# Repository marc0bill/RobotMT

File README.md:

# Project Robot Polytech département MT

Le projet consiste à réaliser un robot automne de type "coupe de France de robotique (Eurobot)".
Le robot MT contient une batterie, des moteurs et des capteurs. Des UCEs (Unité de commande électronique) sont mis en place pour gérer les différents périphériques du robot. Ces UCEs ou ECU(acronyme Anglais) se communiquent par le bus CAN. Le choix du protocole CAN est expliqué dans les Wikis.  

## Getting Started
Vous trouvez dans le dossier de ce projet:
-le dossier "carte": les schémas des UCEs employées.
-le dossier "Firmware": les firmwares des UCEs codé en C. (le principe de la compilation conditionnelle est utilisé dans le code => Un seul projet.X peut servir pour implémenter deux firmware différents sur deux UCEs différentes. Il suffit de de changer le nom du node dans le fichier node.h du projet.X )
-Le dossier python: Les codes pythons utilisées.

### Prerequisites

Logiciel à télécharger:

On utilise des contrôleurs de type dsPIC33FJ128MC804(digital signal controler) (Microchip), il faudrait donc télécharger :
```
MPLAPX IDE
```

```
Compilateur XC16
```

Des schémas électriques des UCEs sont disponible en format .pdf, mais si vous souhaitez les modifier ou voir une vision plus profonde, il faudrait télécharger :
```
EAGLE
```

Pour visualiser les données reçus par l'UART sur votre PC, téléchargez une application terminale simple de porte série 
```
Termite
```
ou
```
CoolTerm
```

=======
# Projet Robot Polytech département MT

Le département Microélectronique et Télécommunications de Polytech Marseille développe son propre robot de A à Z. Chaque année le projet s'améliore grâce aux élèves de 4ème année. Ce robot, de type coupe de France de robotique, peut se déplacer de façon autonome dans son environnement, déplacer des objets, et ramasser des balles (tennis ou ping-pong).

## Getting Started

These instructions will get you a copy of the project up and running on your local machine for development and testing purposes. See deployment for notes on how to deploy the project on a live system.

### Prerequisites

What things you need to install the software and how to install them

```
Give examples
```

### Installing

A step by step series of examples that tell you have to get a development env running

Say what the step will be

```
Give the example
```

And repeat

```
until finished
```

End with an example of getting some data out of the system or using it for a little demo

## Running the tests

Explain how to run the automated tests for this system

### Break down into end to end tests

Explain what these tests test and why

```
Give an example
```

### And coding style tests

Explain what these tests test and why

```
Give an example
```

## Contributing

Please read [CONTRIBUTING.md](https://gist.github.com/PurpleBooth/b24679402957c63ec426) for details on our code of conduct, and the process for submitting pull requests to us.

## Versioning

We use [SemVer](http://semver.org/) for versioning. For the versions available, see the [tags on this repository](https://github.com/your/project/tags). 

## Authors

* **Marc Bocquet** - *Initial work* - [marc0bill](https://github.com/marc0bill)

See also the list of [contributors](https://github.com/your/project/contributors) who participated in this project.

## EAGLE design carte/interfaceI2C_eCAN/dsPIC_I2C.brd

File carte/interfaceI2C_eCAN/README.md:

# Carte interface eCAN/I2C/UART/entrée Analog

## Présentation

La carte proposé ici, permet l'interface entre le bus eCAN et d'autre périférique (comme par exemple les modules ultrason en I2C ou capteur de distance SHARP analogique)

## Détail

Deux versions de cartes sont proposées : 

### dsPIC_I2C

Il s'agit de celle actuellement utilisé et fonctionnelle

### dsPIC_I2CMini

Il s'agit d'une version plus compact à finaliser si nécessaire.
Un travail sur les connecteurs pourrait aussi être effectuer pour amélioré la robustesse d'assemblage et la taille de la carte.

### firmware

Le firmware associé a cette carte est :

```
firmware/dsPICeCAN.X
```

## Authors

* **Marc Bocquet** - *Initial work* - [marc0bill](https://github.com/marc0bill)

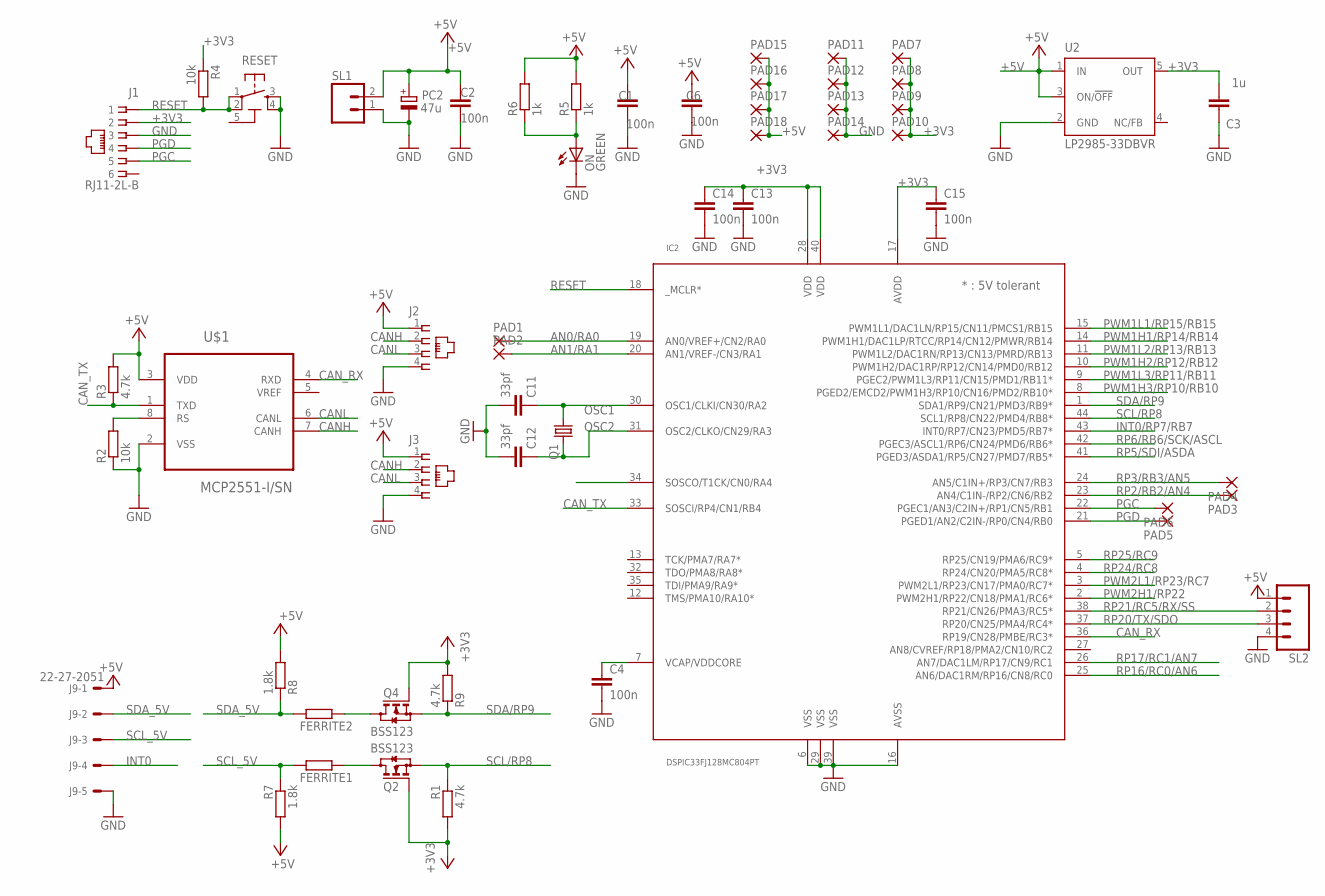
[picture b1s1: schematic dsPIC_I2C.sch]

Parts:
C1, C2: 100n; C0603-ROUND
C3: 1u; C0603-ROUND
C4, C6: 100n; C0603K
C11, C12: 33pf; C0603
C13, C14, C15: 100n; C0603
FERRITE1, FERRITE2: R-EU_M0805; M0805
IC2: DSPIC33FJ128MC804PT; TQFP44
J1: RJ11-2L-B; RJ11-NO_SHIELD
J2, J3: 520249-2
J9: 22-27-2051; 6410-05
ON: GREEN; CHIP-LED0805
PAD1, PAD2, PAD3, PAD4, PAD5, PAD6, PAD7, PAD8, PAD9, PAD10, PAD11, PAD12, PAD13, PAD14, PAD15, PAD16, PAD17, PAD18: 1,6/0,9
PC2: 47u; PANASONIC_D
Q1: CRYSTALSM49; SM49
Q2, Q4: BSS123; SOT23
R1, R3, R9: 4.7k; R0805
R2, R4: 10k; R0805
R5, R6: 1k; R0805
R7, R8: 1.8k; 0204/7
RESET: TS42031-160R-TR-7260; TS42
SL1: M02; 02P
SL2: M04; 04P
U2: LP2985-33DBVR; SOT23-DBV
U$1: MCP2551-I/SN; SOIC127P600X175-8N

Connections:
5-GND: RESET.5 (5-GND)
+3V3: C3.2, C13.1, C14.1, C15.1, IC2.17 (AVDD), IC2.28 (VDD), IC2.40 (VDD), J1.2, PAD7.1, PAD8.1, PAD9.1, PAD10.1, Q2.1 (G), Q4.1 (G), R1.2, R4.1, R9.2, U2.5 (OUT)
+5V: C1.2, C2.2, C6.2, J2.1, J3.1, J9.1, PAD15.1, PAD16.1, PAD17.1, PAD18.1, PC2.+, R3.2, R5.2, R6.2, R7.2, R8.2, SL1.2, SL2.1, U2.1 (IN), U2.3 (ON/!OFF), U$1.3 (VDD)
AN0/RA0: IC2.19 (AN0/VREF+/CN2/RA0), PAD1.1
AN1/RA1: IC2.20 (AN1/VREF-/CN3/RA1), PAD2.1
ASCL: FERRITE1.2, Q2.3 (D)
ASDA: FERRITE2.2, Q4.3 (D)
CANH: J2.2, J3.2, U$1.7 (CANH)
CANL: J2.3, J3.3, U$1.6 (CANL)
CAN_RX: IC2.36 (RP19/CN28/PMBE/RC3*), U$1.4 (RXD)
CAN_TX: IC2.33 (SOSCI/RP4/CN1/RB4), R3.1, U$1.1 (TXD)
GND: C1.1, C2.1, C3.1, C4.2, C6.1, C11.2, C12.2, C13.2, C14.2, C15.2, IC2.6 (VSS), IC2.16 (AVSS), IC2.29 (VSS), IC2.39 (VSS), J1.3, J2.4, J3.4, J9.5, ON.C, PAD11.1, PAD12.1, PAD13.1, PAD14.1, PC2.-, R2.1, RESET.3, RESET.4, SL1.1, SL2.4, U2.2 (GND), U$1.2 (VSS)
INT0: J9.4
INT0/RP7/RB7: IC2.43 (INT0/RP7/CN23/PMD5/RB7*)
unnamed: ON.A, R5.1, R6.1
unnamed: C4.1, IC2.7 (VCAP/VDDCORE)
unnamed: R2.2, U$1.8 (RS)
OSC1: C11.1, IC2.30 (OSC1/CLKI/CN30/RA2), Q1.1
OSC2: C12.1, IC2.31 (OSC2/CLKO/CN29/RA3), Q1.2
PGC: IC2.22 (PGEC1/AN3/C2IN+/RP1/CN5/RB1), J1.5, PAD6.1
PGD: IC2.21 (PGED1/AN2/C2IN-/RP0/CN4/RB0), J1.4, PAD5.1
PWM1H1/RP14/RB14: IC2.14 (PWM1H1/DAC1LP/RTCC/RP14/CN12/PMWR/RB14)
PWM1H2/RP12/RB12: IC2.10 (PWM1H2/DAC1RP/RP12/CN14/PMD0/RB12)
PWM1H3/RP10/RB10: IC2.8 (PGED2/EMCD2/PWM1H3/RP10/CN16/PMD2/RB10*)
PWM1L1/RP15/RB15: IC2.15 (PWM1L1/DAC1LN/RP15/CN11/PMCS1/RB15)
PWM1L2/RP13/RB13: IC2.11 (PWM1L2/DAC1RN/RP13/CN13/PMRD/RB13)
PWM1L3/RP11/RB11: IC2.9 (PGEC2/PWM1L3/RP11/CN15/PMD1/RB11*)
PWM2H1/RP22: IC2.2 (PWM2H1/RP22/CN18/PMA1/RC6*)
PWM2L1/RP23/RC7: IC2.3 (PWM2L1/RP23/CN17/PMA0/RC7*)
RESET: IC2.18 (_MCLR*), J1.1, R4.2, RESET.1, RESET.2
RP2/RB2/AN4: IC2.23 (AN4/C1IN-/RP2/CN6/RB2), PAD3.1
RP3/RB3/AN5: IC2.24 (AN5/C1IN+/RP3/CN7/RB3), PAD4.1
RP5/SDI/ASDA: IC2.41 (PGED3/ASDA1/RP5/CN27/PMD7/RB5*)
RP6/RB6/SCK/ASCL: IC2.42 (PGEC3/ASCL1/RP6/CN24/PMD6/RB6*)
RP16/RC0/AN6: IC2.25 (AN6/DAC1RM/RP16/CN8/RC0)
RP17/RC1/AN7: IC2.26 (AN7/DAC1LM/RP17/CN9/RC1)
RP20/TX/SDO: IC2.37 (RP20/CN25/PMA4/RC4*), SL2.3
RP21/RC5/RX/SS: IC2.38 (RP21/CN26/PMA3/RC5*), SL2.2
RP24/RC8: IC2.4 (RP24/CN20/PMA5/RC8*)
RP25/RC9: IC2.5 (RP25/CN19/PMA6/RC9*)
SCL/RP8: IC2.44 (SCL1/RP8/CN22/PMD4/RB8*), Q2.2 (S), R1.1
SCL_5V: FERRITE1.1, J9.3, R7.1
SDA/RP9: IC2.1 (SDA1/RP9/CN21/PMD3/RB9*), Q4.2 (S), R9.1
SDA_5V: FERRITE2.1, J9.2, R8.1

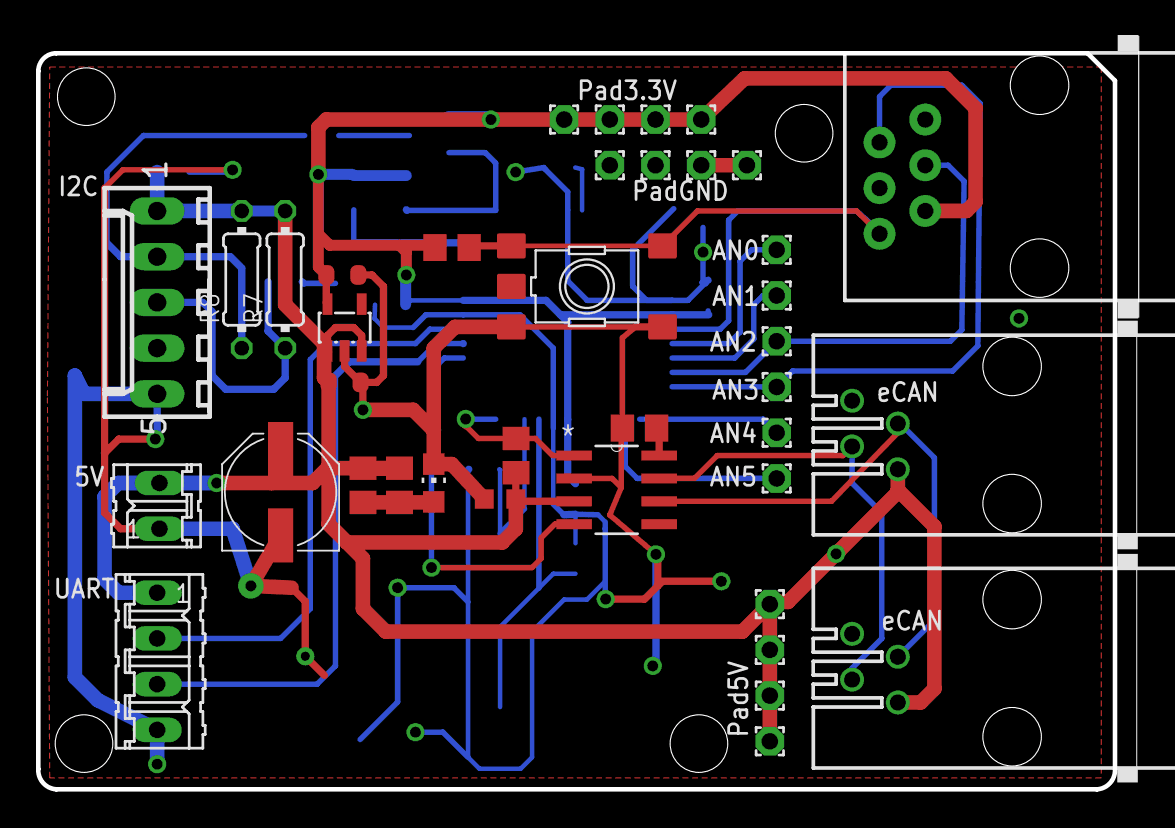
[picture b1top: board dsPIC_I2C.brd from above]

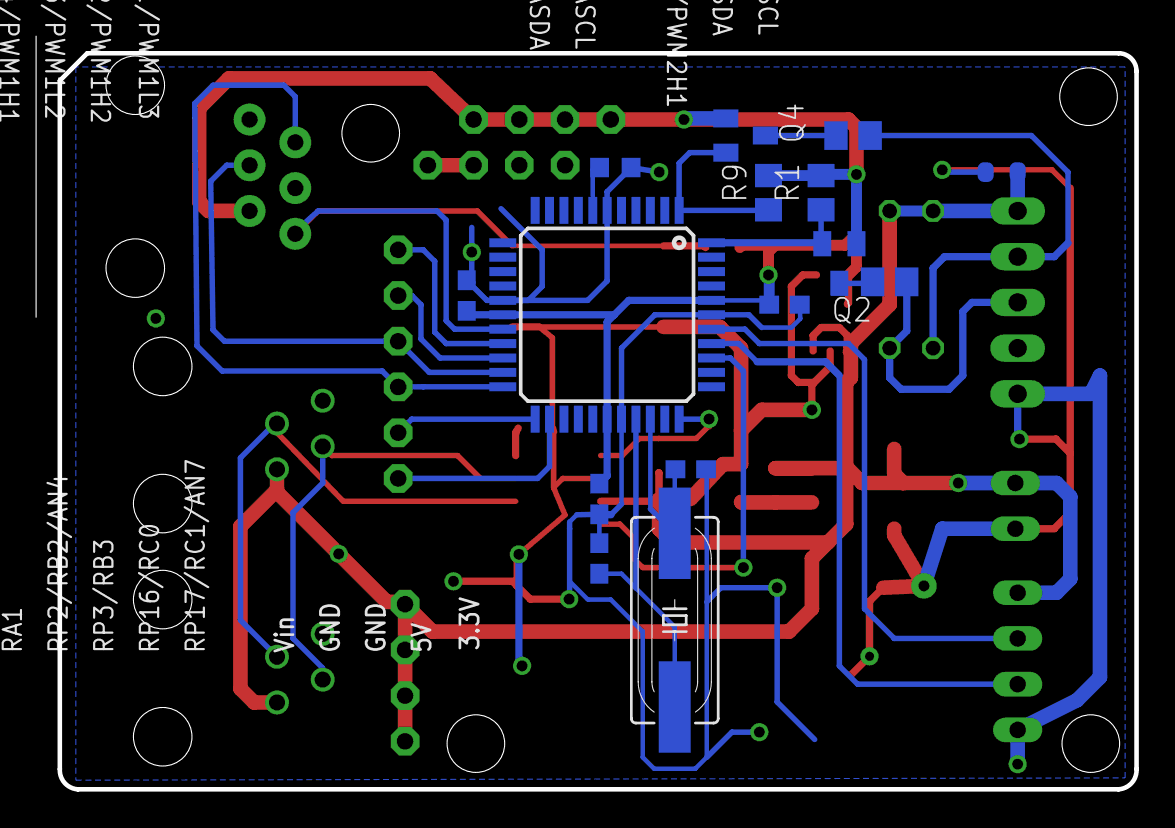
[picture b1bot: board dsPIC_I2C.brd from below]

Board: 2 copper layers, 61.0 x 41.7 mm, 54 parts (15 on the bottom side), 27 nets.

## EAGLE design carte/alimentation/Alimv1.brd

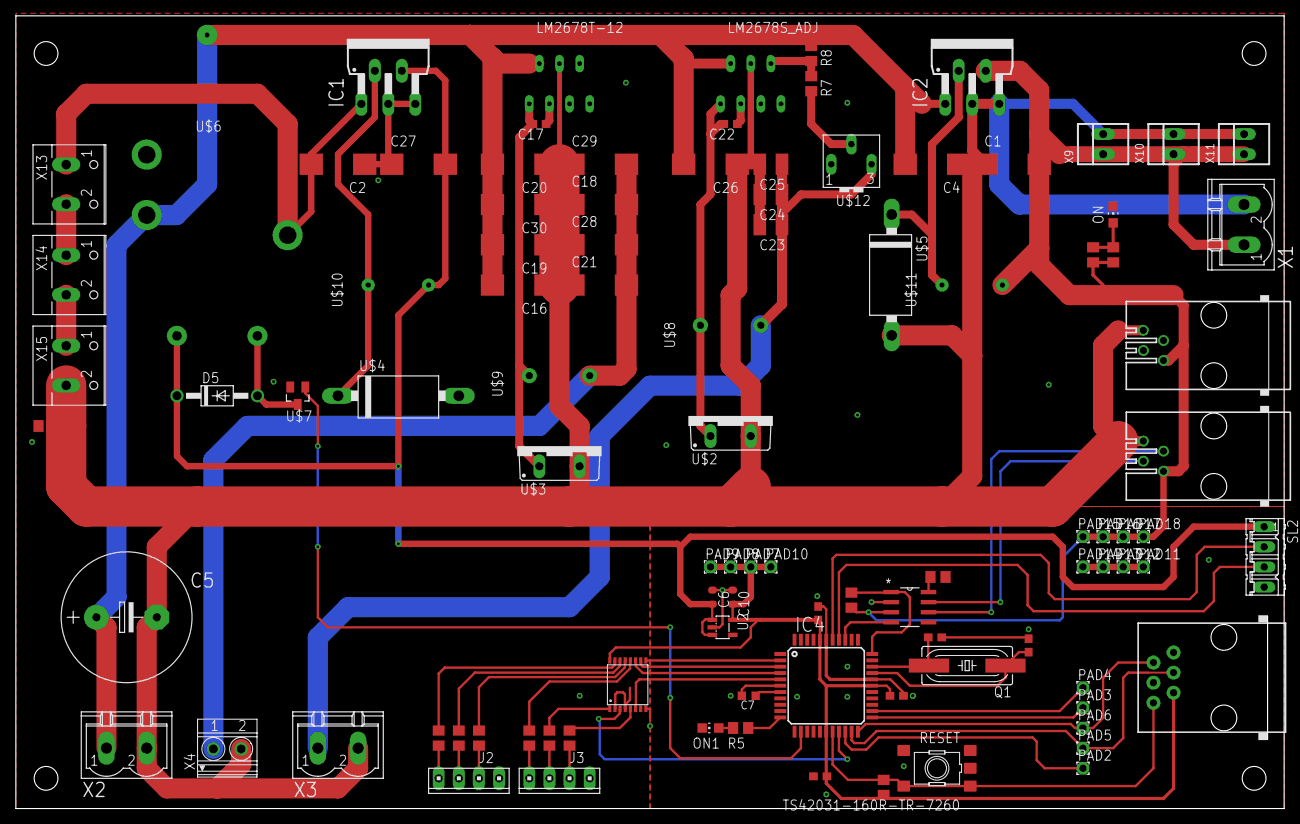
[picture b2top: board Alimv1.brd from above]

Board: 2 copper layers, 160.0 x 100.0 mm, 99 parts (0 on the bottom side), 57 nets.

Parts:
C1, C27: 220uF; D/7343-31W
C2, C4: 330uF; D/7343-31W
C5: 1000uF; E7,5-16
C6: 100n; C0603-ROUND
C7: 100n; C0603K
C10: 1u; C0603-ROUND
C11, C12: 33pf; C0603
C13, C14, C15: 100n; C0603
C16, C19, C20, C26, C30: 10uF; D/7343-31W
C17, C22: 0.01uF; C0603
C18, C21, C28, C29: 68uF; D/7343-31W
C23, C24, C25: 100uF; C1210
D5: 1N4004; DO41-10
IC1, IC2: LM2596T; T05D
IC4: DSPIC33FJ128MC804PT; TQFP44
J2, J3: 10X04MTA
J4: RJ11-2L-B; RJ11-NO_SHIELD
J5, J6: 520249-2
LM2678S_ADJ, LM2678T-12: TO-220-7
ON, ON1: GREEN; CHIP-LED0805
PAD2, PAD3, PAD4, PAD5, PAD6, PAD7, PAD8, PAD9, PAD10, PAD11, PAD12, PAD13, PAD14, PAD15, PAD16, PAD17, PAD18: 1,6/0,9
Q1: SM49
R1, R6, R8: 1k; R0805
R2, R4: 10k; R0805
R3: 4.7k; R0805
R5: 500; R0805
R7: 4.12k; R0805
R9, R10, R11, R12, R13, R14: 20k; R0805
R15: 0; R0805
RESET: TS42031-160R-TR-7260; TS42
SL2: 04P
U2: LP2985-33DBVR; SOT23-DBV
U$1: MCP2551-I/SN; SOIC127P600X175-8N
U$2, U$3: TO220ACS
U$4, U$5: DO-201AD
U$6: T9GV1L14-5; T9G
U$7: BSH108; SOT23
U$8: 22.8uH; KM-3.0
U$9: 14.8uH; KM-2.1
U$10, U$11: 53uH; KM-3.0_5V3A
U$12: RJ26FX102; RJ6S
U$13: NX3L4051PW; SOT403
X1, X2, X3: MSTBV2
X4: 1751248
X9, X10, X11: 22-23-2021
X13, X14, X15: W237-102

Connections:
5V_3A: C1.+, IC2.4, J5.1, J6.1, PAD15.1, PAD16.1, PAD17.1, PAD18.1, R1.2, R3.2, R6.2, U$1.3, U$11.2, X1.1, X9.1, X10.1, X11.1
22V: C4.+, C5.+, C16.+, C19.+, C20.+, C26.+, C30.+, IC2.1, LM2678S_ADJ.2, LM2678T-12.2, R8.1, U$6.K, X2.1
+3V3: C10.2, C13.1, C14.1, C15.1, IC4.17, IC4.28, IC4.40, J4.2, PAD7.1, PAD8.1, PAD9.1, PAD10.1, R4.1, U2.5, U$13.P$16
+5V_µC: C6.2, C27.+, D5.C, IC1.4, SL2.1, U2.1, U2.3, U$6.B1, U$10.2
AN0/RA0: IC4.19, U$13.P$3
AN1/RA1: IC4.20, PAD2.1
BAT1_3.7V: J3.3, R14.1
BAT1_7.4V: J3.2, R13.1
BAT2_14.8V: J2.3, R11.1
BAT2_18.5V: J2.2, R10.1
BAT3+: C2.+, IC1.1, U$6.A, X13.1
BAT12_11.1V: X14.2, X15.1
BAT12_11V: J2.4, J3.1, R12.1
BAT23_22.2V: X13.2, X14.1
BAT23_22V: J2.1, R9.1
CANH: J5.2, J6.2, U$1.7
CANL: J5.3, J6.3, U$1.6
CAN_RX: IC4.36, U$1.4
CAN_TX: IC4.33, R3.1, U$1.1
GND: C2.-, C6.1, C7.2, C10.1, C11.2, C12.2, C13.2, C14.2, C15.2, C27.-, IC1.3, IC1.5, IC4.6, IC4.16, IC4.29, IC4.39, J3.4, J4.3, ON.C, ON1.C, PAD11.1, PAD12.1, PAD13.1, PAD14.1, R2.1, R15.1, RESET.3, RESET.4, SL2.4, U2.2, U$1.2, U$4.A, U$7.2, U$13.P$2, U$13.P$4, U$13.P$8
GND_POW: C1.-, C4.-, C5.-, C16.-, C18.-, C19.-, C20.-, C21.-, C23.2, C24.2, C25.2, C26.-, C28.-, C29.-, C30.-, IC2.3, IC2.5, J5.4, J6.4, LM2678S_ADJ.4, LM2678T-12.4, R15.2, U$2.A, U$3.A, U$5.A, X1.2, X2.2, X3.2, X4.2, X9.2, X10.2, X11.2, X15.2
unnamed: ON1.A, R5.2
unnamed: ON.A, R1.1, R6.1
unnamed: R9.2, U$13.P$15
unnamed: C7.1, IC4.7
unnamed: R11.2, U$13.P$13
unnamed: LM2678S_ADJ.6, R7.1, R8.2
unnamed: R2.2, U$1.8
unnamed: IC2.2, U$5.C, U$11.1
unnamed: C17.2, LM2678T-12.1, U$3.C, U$9.1
unnamed: IC1.2, U$4.C, U$10.1
unnamed: C22.1, LM2678S_ADJ.3
unnamed: C17.1, LM2678T-12.3
unnamed: R12.2, U$13.P$12
unnamed: C22.2, LM2678S_ADJ.1, U$2.C, U$8.1
unnamed: C23.1, C24.1, C25.1, U$8.2, U$12.E, X3.1
unnamed: D5.A, U$6.B2, U$7.3
unnamed: R7.2, U$12.S
unnamed: R13.2, U$13.P$1
unnamed: R10.2, U$13.P$14
unnamed: R14.2, U$13.P$5
OSC1: C11.1, IC4.30, Q1.1
OSC2: C12.1, IC4.31, Q1.2
PGC: IC4.22, J4.5, PAD6.1
PGD: IC4.21, J4.4, PAD5.1
PWM1L2/RP13/RB13: IC4.11, R5.1
PWM2H1/RP22: IC4.2, U$13.P$9
PWM2L1/RP23/RC7: IC4.3, U$13.P$10
RA7: IC4.13, U$7.1
RESET: IC4.18, J4.1, R4.2, RESET.1, RESET.2
RP2/RB2/AN4: IC4.23, PAD3.1
RP3/RB3/AN5: IC4.24, PAD4.1
RP20/TX/SDO: IC4.37, SL2.3
RP21/RC5/RX/SS: IC4.38, SL2.2
RP24/RC8: IC4.4, U$13.P$11
RP25/RC9: IC4.5, U$13.P$6
V+: C18.+, C21.+, C28.+, C29.+, U$9.2, X4.1

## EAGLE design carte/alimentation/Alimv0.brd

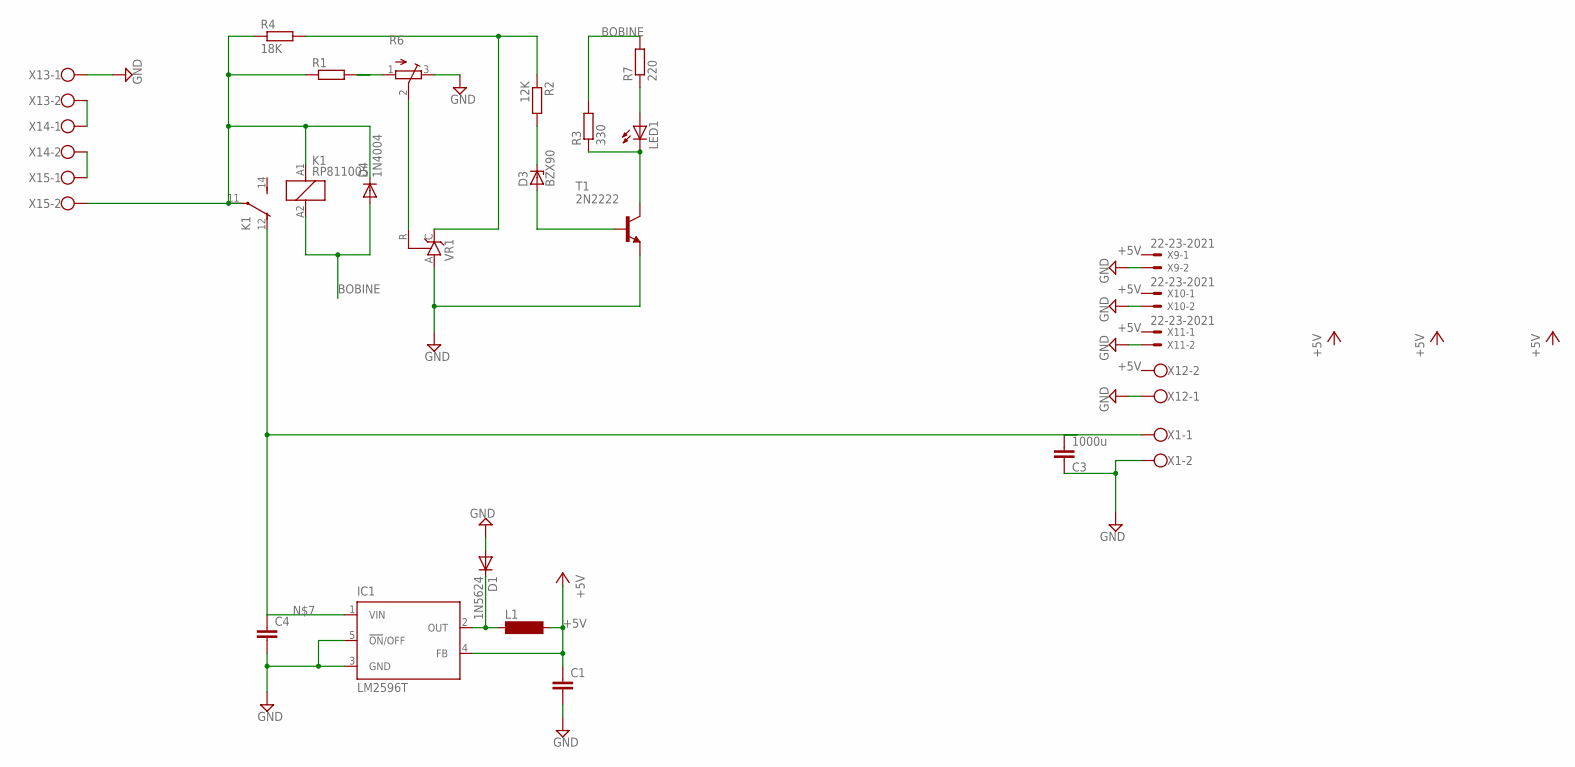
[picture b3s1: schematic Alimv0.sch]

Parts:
C1, C4: C-EUC0603; C0603
C3: 1000u; C0603
D1: 1N5624; DO201-15
D3: BZX90; DO34Z7
D4: 1N4004; DO41-10
IC1: LM2596T; T05D
K1: RP811005; RT-C/O12A5
L1: SM-L15A
LED1: LED_E; LED_1206
R1: R-EU_R0805; R0805
R2: 12K; R0805
R3: 330; R0805
R4: 18K; R0805
R6: TRIM_EU-3223G; 3223G
R7: 220; R0805
T1: 2N2222; TO18
VR1: TL431CLP; TO92-CLP
X1, X12, X13, X14, X15: W237-102
X9, X10, X11: 22-23-2021

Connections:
+5V: C1.1, IC1.4 (FB), L1.2
BOB: D4.C, K1.11, K1.A1 (1), R1.1, R4.1, X15.2
BOBINE: D4.A, K1.A2 (2), R3.2, R7.2
GND: C1.2, C3.1, C4.2, D1.A, IC1.3 (GND), IC1.5 (!ON!/OFF), R6.3 (E), T1.1 (E), VR1.A, X1.2, X9.2, X10.2, X11.2, X12.1
unnamed: X13.2, X14.1
unnamed: X14.2, X15.1
unnamed: R1.2, R6.1 (A)
unnamed: C4.1, IC1.1 (VIN)
unnamed: D3.C, R2.2
unnamed: D3.A, T1.2 (B)
unnamed: D1.C, IC1.2 (OUT), L1.1
unnamed: C3.2, X1.1
unnamed: LED1.A, R7.1
unnamed: R6.2 (S), VR1.R
unnamed: LED1.C, R3.1, T1.3 (C)
unnamed: R2.1, R4.2, VR1.C

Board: 2 copper layers, 26 parts (0 on the bottom side), 16 nets, no tracks yet.

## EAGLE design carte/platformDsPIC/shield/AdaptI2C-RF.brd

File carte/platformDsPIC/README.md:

# Carte platforme dsPIC (eCAN <=> UART)

## Présentation

La carte proposée ici, permet de réaliser une passerelle eCAN <=> UART.

## Détail
On utlise cette carte comme platforme de monitoring et commande de l'ensemble des nodes connectés sur le bus CAN. Elle écoute les messages transmis sur le bus CAN et les envoient par le bus UART à un PC par exemple pour ces messages en format char sur un terminal(Termite, CoolTerm, etc).

### firmware

Le firmware associé a cette carte est :

```
firmware/dsPICeCAN.X
```

## Authors

* **Marc Bocquet** - *Initial work* - [marc0bill](https://github.com/marc0bill)

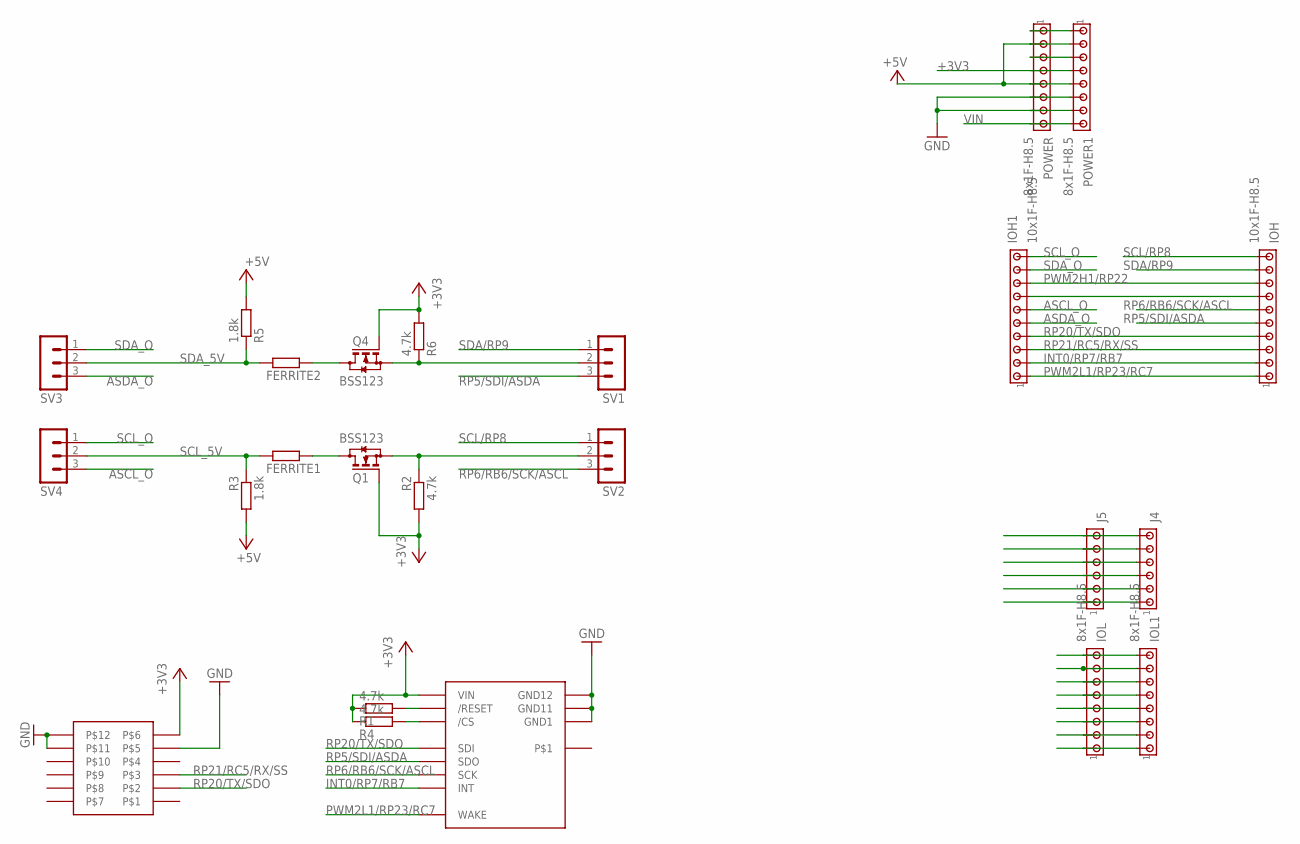
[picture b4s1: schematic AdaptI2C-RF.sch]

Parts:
FERRITE1, FERRITE2: R-EU_M0805; M0805
IOH, IOH1: 10x1F-H8.5; 10X10MTA
IOL, IOL1: 8x1F-H8.5; 10X08MTA
J4, J5: MTA06-100; 10X06MTA
POWER, POWER1: 8x1F-H8.5; 10X08MTA
Q1, Q4: BSS123; SOT23
R1, R2, R4, R6: 4.7k; R0805
R3, R5: 1.8k; 0204/7
SV1, SV2, SV3, SV4: MA03-1
U$2: MRF24J40MA
U$7: PMOD2X6

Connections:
+3V3: POWER.4, POWER1.4, Q1.1 (G), Q4.1 (G), R1.1, R2.2, R4.1, R6.2, U$2.P$10 (VIN), U$7.P$6
+5V: POWER.2, POWER.5, POWER1.2, POWER1.5, R3.2, R5.2
AN0/RA0: J4.1 (6), J5.1 (6)
AN1/RA1: J4.2 (5), J5.2 (5)
ASCL: FERRITE1.2, Q1.3 (D)
ASCL_O: IOH1.6, SV4.3
ASDA: FERRITE2.2, Q4.3 (D)
ASDA_O: IOH1.5, SV3.3
GND: POWER.6, POWER.7, POWER1.6, POWER1.7, U$2.P$1 (GND1), U$2.P$11 (GND11), U$2.P$12 (GND12), U$7.P$5, U$7.P$11, U$7.P$12
INT0/RP7/RB7: IOH.2, IOH1.2, U$2.P$4 (INT)
unnamed: POWER.1, POWER1.1
unnamed: POWER.3, POWER1.3
unnamed: IOH.7, IOH1.7
unnamed: R1.2, U$2.P$2 (/RESET)
unnamed: Q1.2 (S), R2.1, SV2.2
unnamed: Q4.2 (S), R6.1, SV1.2
PWM1H1/RP14/RB14: IOL.2, IOL1.2
PWM1H2/RP12/RB12: IOL.4, IOL1.4
PWM1H3/RP10/RB10: IOL.6, IOL1.6
PWM1L1/RP15/RB15: IOL.1, IOL1.1
PWM1L2/RP13/RB13: IOL.3, IOL1.3
PWM1L3/RP11/RB11: IOL.5, IOL1.5
PWM2H1/RP22: IOH.8, IOH1.8
PWM2L1/RP23/RC7: IOH.1, IOH1.1, U$2.P$3 (WAKE)
RP2/RB2/AN4: J4.3 (4), J5.3 (4)
RP3/RB3/AN5: J4.4 (3), J5.4 (3)
RP5/SDI/ASDA: IOH.5, SV1.3, U$2.P$7 (SDO)
RP6/RB6/SCK/ASCL: IOH.6, SV2.3, U$2.P$6 (SCK)
RP16/RC0/AN6: J4.5 (2), J5.5 (2)
RP17/RC1/AN7: J4.6 (1), J5.6 (1)
RP20/TX/SDO: IOH.4, IOH1.4, U$2.P$5 (SDI), U$7.P$2
RP21/RC5/RX/SS: IOH.3, IOH1.3, R4.2, U$2.P$8 (/CS), U$7.P$3
RP24/RC8: IOL.8, IOL1.8
RP25/RC9: IOL.7, IOL1.7
SCL/RP8: IOH.10, SV2.1
SCL_5V: FERRITE1.1, R3.1, SV4.2
SCL_O: IOH1.10, SV4.1
SDA/RP9: IOH.9, SV1.1
SDA_5V: FERRITE2.1, R5.1, SV3.2
SDA_O: IOH1.9, SV3.1
VIN: POWER.8, POWER1.8

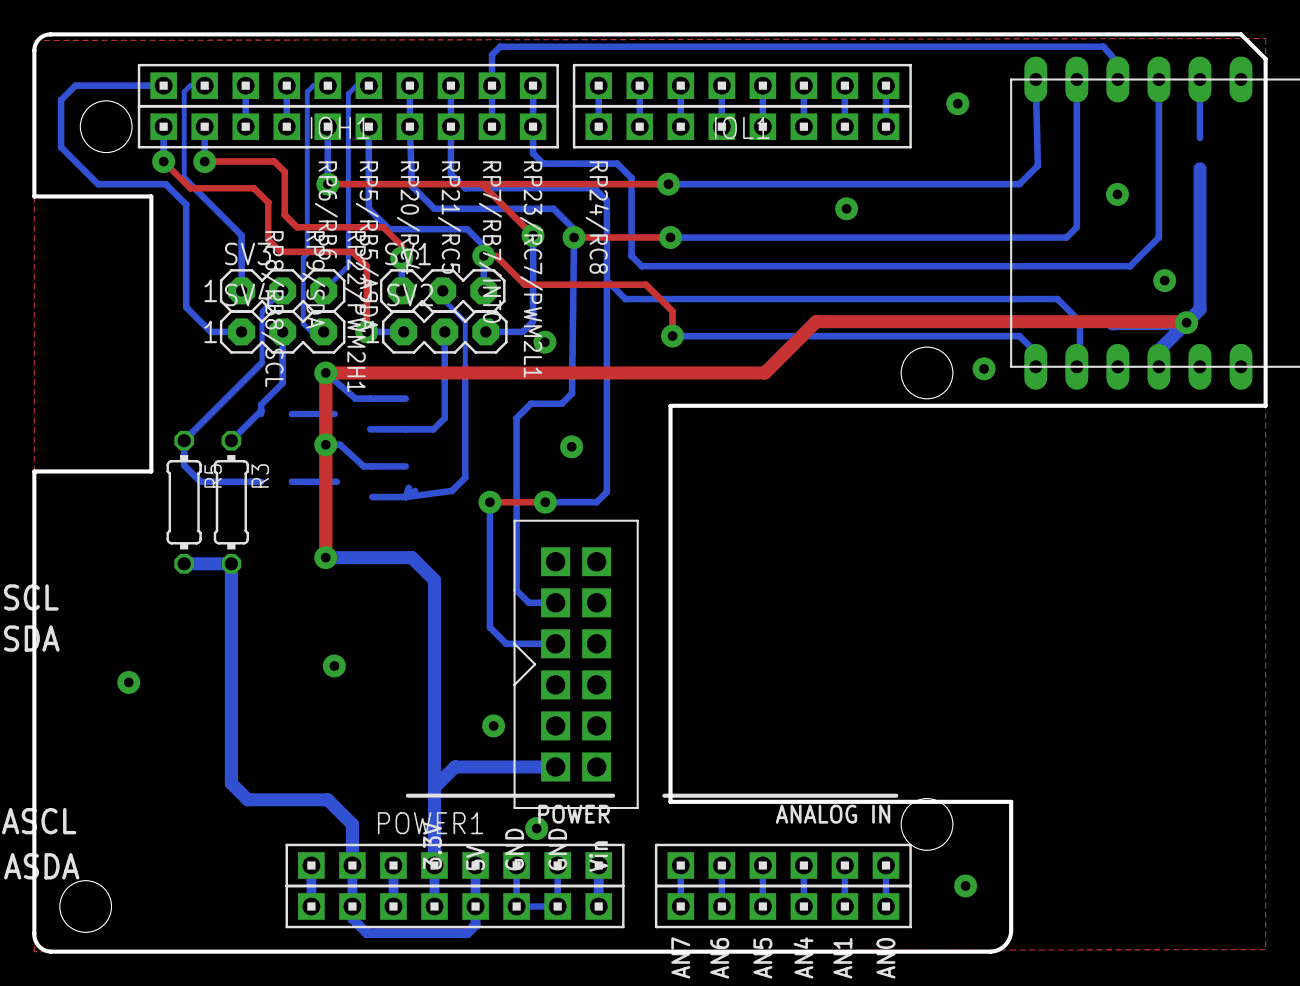
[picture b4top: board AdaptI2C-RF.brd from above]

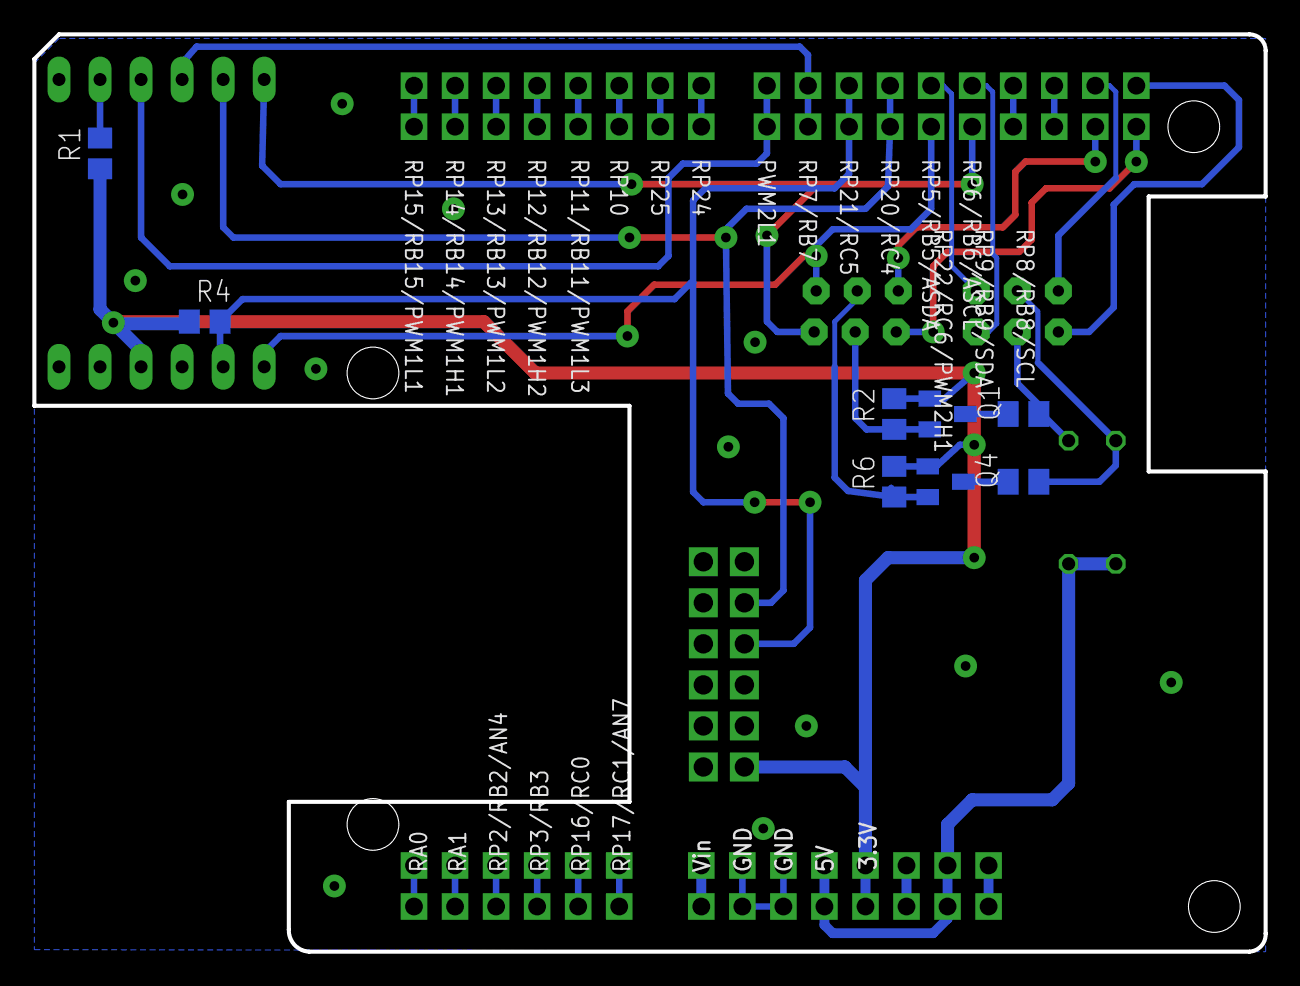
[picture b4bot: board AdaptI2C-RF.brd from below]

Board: 2 copper layers, 76.2 x 56.8 mm, 24 parts (8 on the bottom side), 41 nets.

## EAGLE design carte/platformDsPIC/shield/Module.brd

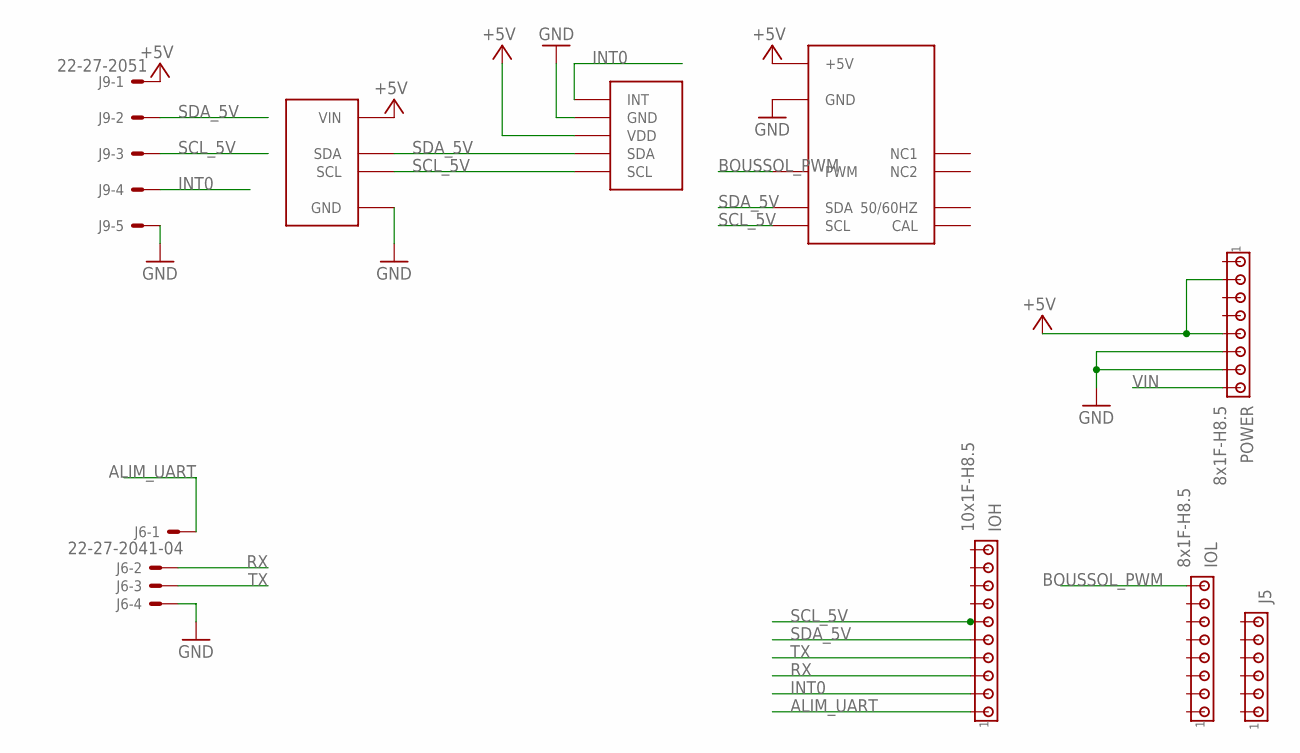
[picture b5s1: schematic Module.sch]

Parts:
IOH: 10x1F-H8.5; 10X10MTA
IOL: 8x1F-H8.5; 10X08MTA
J5: MTA06-100; 10X06MTA
J6: 22-27-2041-04; 6410-04
J9: 22-27-2051; 6410-05
POWER: 8x1F-H8.5; 10X08MTA
U$1: SRF10
U$2: MPU9150
U$6: CMPS03

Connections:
+5V: J9.1, POWER.2, POWER.5, U$1.P$4 (VIN), U$2.P$3 (VDD), U$6.P$1 (+5V)
ALIM_UART: IOH.1, J6.1
BOUSSOL_PWM: IOL.8, U$6.P$4 (PWM)
GND: J6.4, J9.5, POWER.6, POWER.7, U$1.P$1 (GND), U$2.P$2 (GND), U$6.P$9 (GND)
INT0: IOH.2, J9.4, U$2.P$1 (INT)
RX: IOH.3, J6.2
SCL_5V: IOH.6, J9.3, U$1.P$2 (SCL), U$2.P$5 (SCL), U$6.P$2 (SCL)
SDA_5V: IOH.5, J9.2, U$1.P$3 (SDA), U$2.P$4 (SDA), U$6.P$3 (SDA)
TX: IOH.4, J6.3
VIN: POWER.8

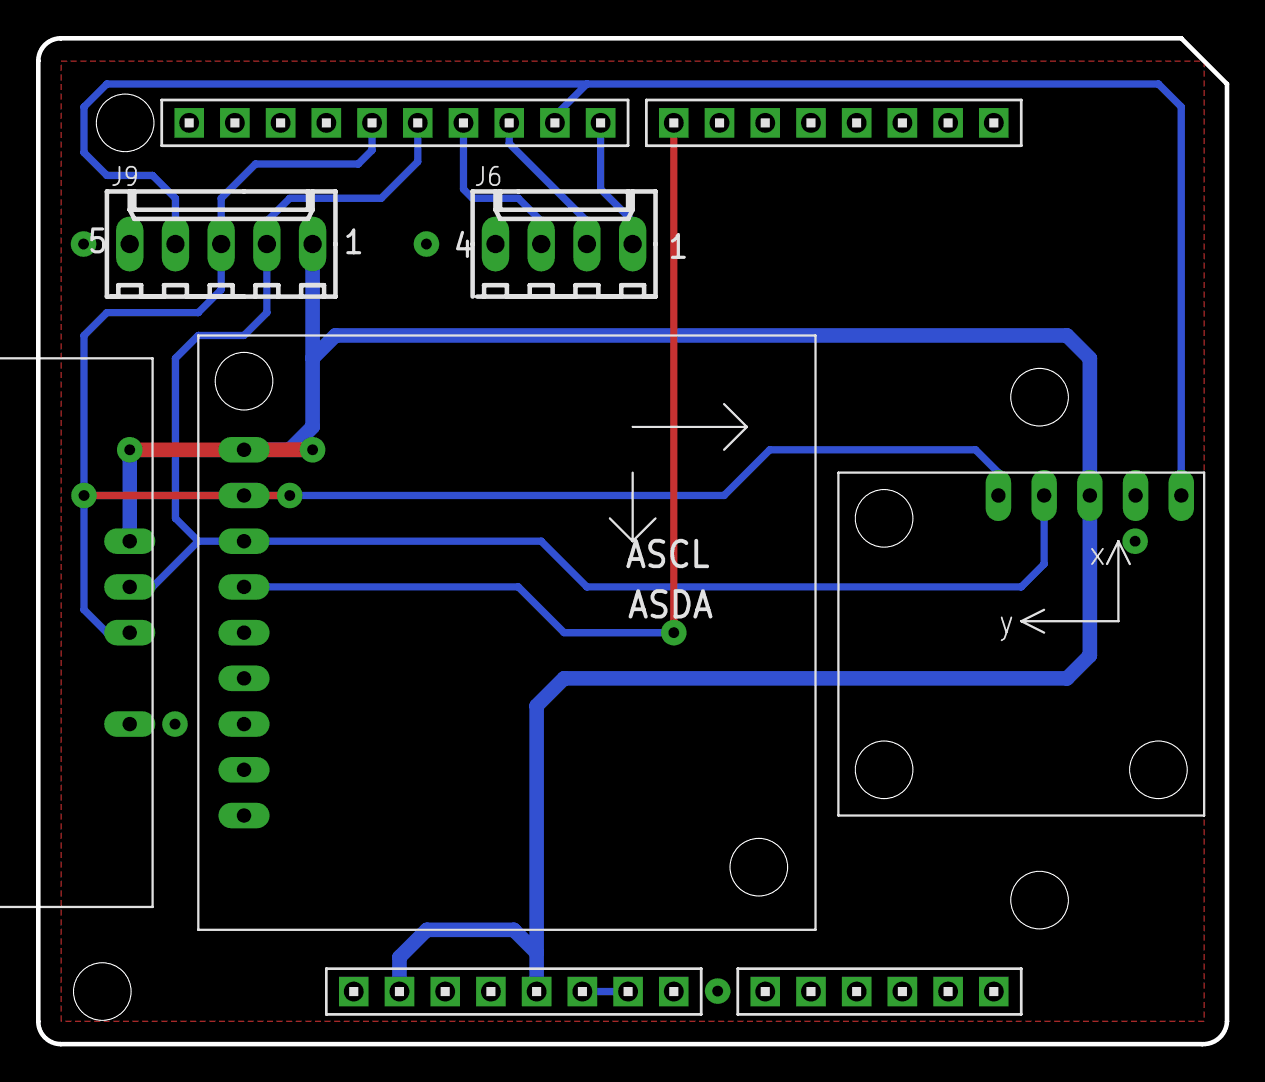
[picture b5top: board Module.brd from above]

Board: 2 copper layers, 66.0 x 55.9 mm, 9 parts (0 on the bottom side), 9 nets.

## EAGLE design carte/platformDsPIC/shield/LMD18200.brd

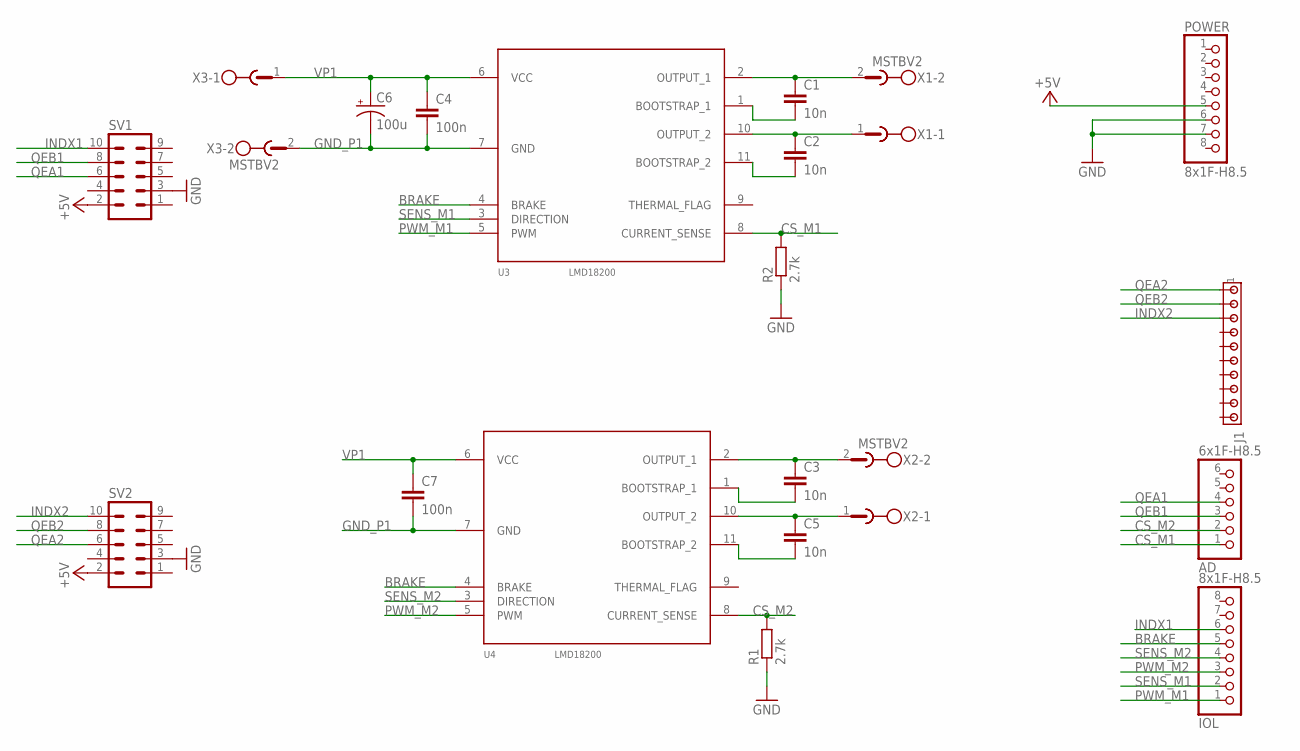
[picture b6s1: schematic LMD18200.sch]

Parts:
AD: 6x1F-H8.5; 1X06
C1, C2, C3, C5: 10n; C0603
C4, C7: 100n; C0603
C6: 100u; E5-13
IOL: 8x1F-H8.5; 1X08
J1: MTA10-100; 10X10MTA
POWER: 8x1F-H8.5; 1X08
R1, R2: 2.7k; R0805
SV1, SV2: ML10L
U3, U4: LMD18200; TO-220-11_C
X1, X2, X3: MSTBV2

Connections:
+5V: POWER.5, SV1.2, SV2.2
BRAKE: IOL.5, U3.4 (BRAKE), U4.4 (BRAKE)
CS_M1: AD.1, R2.2, U3.8 (CURRENT_SENSE)
CS_M2: AD.2, R1.2, U4.8 (CURRENT_SENSE)
GND: POWER.6, POWER.7, R1.1, R2.1, SV1.3, SV2.3
GND_P1: C4.2, C6.-, C7.2, U3.7 (GND), U4.7 (GND), X3.2
INDX1: IOL.6, SV1.10
INDX2: J1.3, SV2.10
unnamed: C2.2, U3.11 (BOOTSTRAP_2)
unnamed: C1.2, U3.1 (BOOTSTRAP_1)
unnamed: C1.1, U3.2 (OUTPUT_1), X1.2
unnamed: C2.1, U3.10 (OUTPUT_2), X1.1
unnamed: C3.1, U4.2 (OUTPUT_1), X2.2
unnamed: C5.1, U4.10 (OUTPUT_2), X2.1
unnamed: C3.2, U4.1 (BOOTSTRAP_1)
unnamed: C5.2, U4.11 (BOOTSTRAP_2)
PWM_M1: IOL.1, U3.5 (PWM)
PWM_M2: IOL.3, U4.5 (PWM)
QEA1: AD.4, SV1.6
QEA2: J1.1, SV2.6
QEB1: AD.3, SV1.8
QEB2: J1.2, SV2.8
SENS_M1: IOL.2, U3.3 (DIRECTION)
SENS_M2: IOL.4, U4.3 (DIRECTION)
VP1: C4.1, C6.+, C7.1, U3.6 (VCC), U4.6 (VCC), X3.1
